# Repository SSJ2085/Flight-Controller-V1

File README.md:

# Flight-Controller-V1
This is a design of a flight controller for the  small 4'' to 5'' UAV.

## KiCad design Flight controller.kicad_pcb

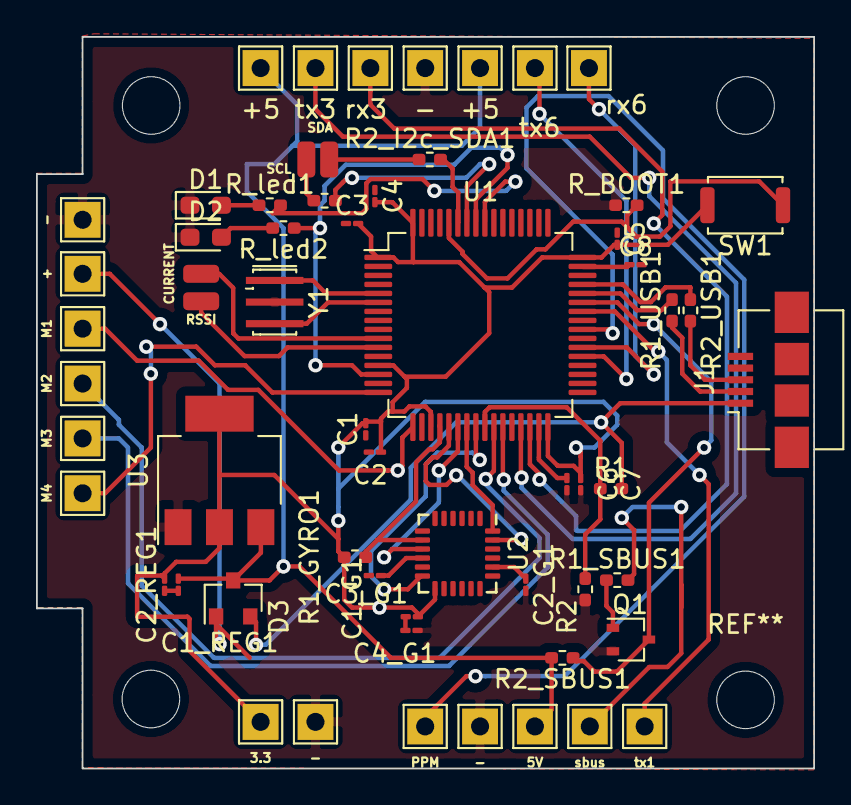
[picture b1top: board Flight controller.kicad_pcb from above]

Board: 2 copper layers, 43.2 x 40.6 mm, 60 parts (0 on the bottom side), 46 nets.

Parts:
3.3: 4; TestPoint_THTPad_2.0x2.0mm_Drill1.0mm
5V: TestPoint_THTPad_2.0x2.0mm_Drill1.0mm
+: +; TestPoint_THTPad_2.0x2.0mm_Drill1.0mm
+5, +5#2: TestPoint_THTPad_2.0x2.0mm_Drill1.0mm
-: 4; TestPoint_THTPad_2.0x2.0mm_Drill1.0mm
-#2: TestPoint_THTPad_2.0x2.0mm_Drill1.0mm
-#3: 4; TestPoint_THTPad_2.0x2.0mm_Drill1.0mm
-#4: -; TestPoint_THTPad_2.0x2.0mm_Drill1.0mm
C1, C2, C3, C4, C5, C6, C7, C8: 100nF; C_01005_0402Metric_Pad0.57x0.30mm_HandSolder
C1_G1, C3_G1: 0.1uF; C_01005_0402Metric_Pad0.57x0.30mm_HandSolder
C1_REG1, C2_REG1: 10uF; C_01005_0402Metric_Pad0.57x0.30mm_HandSolder
C2_G1: 2.2nF; C_01005_0402Metric_Pad0.57x0.30mm_HandSolder
C4_G1: 1uF; C_01005_0402Metric_Pad0.57x0.30mm_HandSolder
CURRENT: SolderWirePad_1x01_SMD_1x2mm
D1: LED_Small; LED_0603_1608Metric_Pad1.05x0.95mm_HandSolder
D2: LED; LED_0603_1608Metric_Pad1.05x0.95mm_HandSolder
D3: BAT54C; SOT-23
J1: USB_B_Micro; USB_Micro-B_Amphenol_10104110_Horizontal
M1: 1; TestPoint_THTPad_2.0x2.0mm_Drill1.0mm
M2: 2; TestPoint_THTPad_2.0x2.0mm_Drill1.0mm
M3: 3; TestPoint_THTPad_2.0x2.0mm_Drill1.0mm
M4: 4; TestPoint_THTPad_2.0x2.0mm_Drill1.0mm
PPM: 4; TestPoint_THTPad_2.0x2.0mm_Drill1.0mm
Q1: BC817W; SOT-323_SC-70
R1, R2: 10k; R_0402_1005Metric_Pad0.72x0.64mm_HandSolder
R1_GYRO1, R1_I2c_SCL1, R2_I2c_SDA1, R2_SBUS1: 10K; R_0402_1005Metric_Pad0.72x0.64mm_HandSolder
R1_SBUS1: 4.7K; R_0402_1005Metric_Pad0.72x0.64mm_HandSolder
R1_USB1, R2_USB1: 22; R_0402_1005Metric_Pad0.72x0.64mm_HandSolder
RSSI: SolderWirePad_1x01_SMD_1x2mm
R_BOOT1: 10k; R_0402_1005Metric_Pad0.72x0.64mm_HandSolder
R_led1, R_led2: 1K; R_0402_1005Metric_Pad0.72x0.64mm_HandSolder
SCL: SolderWirePad_1x01_SMD_1x2mm
SDA: SolderWirePad_1x01_SMD_1x2mm
SW1: SW_Push; SW_Push_SPST_NO_Alps_SKRK
U1: STM32F405RGT6; LQFP-64_10x10mm_P0.5mm
U2: MPU-6000; InvenSense_QFN-24_4x4mm_P0.5mm
U3: NCP1117-3.3_SOT223; SOT-223-3_TabPin2
Y1: 8MHZ; Resonator_SMD_muRata_CSTxExxV-3Pin_3.0x1.1mm_HandSoldering
rx3: TestPoint_THTPad_2.0x2.0mm_Drill1.0mm
rx6: 4; TestPoint_THTPad_2.0x2.0mm_Drill1.0mm
sbus: TestPoint_THTPad_2.0x2.0mm_Drill1.0mm
tx1, tx3, tx6: TestPoint_THTPad_2.0x2.0mm_Drill1.0mm

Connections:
+5V: +.2, D3.1, R2_SBUS1.2
/5V_USB: D3.2, J1.1, R1.2
/CURRENT_PAD: CURRENT.1, U1.10
/GYRO_CS: R1_GYRO1.1, U1.20, U2.8
/GYRO_INT: U1.24, U2.12
/GYRO_SCL: U1.21, U2.23
/GYRO_SDA: U1.23, U2.24
/GYRO_SDO: U1.22, U2.9
/I2C_SCL: R1_I2c_SCL1.1, SCL.1
/I2C_SDA: R2_I2c_SDA1.1, SDA.1
/LED1: R_led1.2, U1.56
/LED2: R_led2.1, U1.14, U1.57
/M1: M1.3, U1.17
/M2: M2.4, U1.26
/M3: M3.5, U1.27
/M4: M4.6, U1.16
/PPM_IN: PPM.PPM, U1.40
/RSSI: RSSI.1, U1.11
/SBUS: R1_SBUS1.2, sbus.1
/UART1_RX: Q1.3, R2_SBUS1.1, U1.43
/UART1_TX: U1.42, tx1.1
/UART3_RX: U1.30, rx3.RX3
/UART3_TX: U1.29, tx3.TX3
/UART6_RX: U1.38, rx6.RX6
/UART6_TX: U1.37, tx6.TX6
/VDD: 3.3.7, C1.2, C2.2, C2_REG1.2, C3.2, C3_G1.1, C4.2, C5.2, C6.2, R1_GYRO1.2, SW1.2, U1.1, U1.13, U1.19, U1.32, U1.48, U1.64, U2.13, U3.2
BOOT: R_BOOT1.2, SW1.1, U1.60
GND: -.6, -#2.GND, -#3.6, -#4.1, C1.1, C1_G1.2, C1_REG1.2, C2.1, C2_G1.2, C2_REG1.1, C3.1, C4.1, C4_G1.2, C5.1, C6.1, C7.1, C8.2, D1.1, D2.1, J1.5, Q1.2, R2.2, R_BOOT1.1, U1.12, U1.18, U1.63, U2.1, U2.11, U2.18, U3.1, Y1.2
unnamed: C1_G1.1, U2.10
unnamed: 5V.1, +5.+5, +5#2.+5, C1_REG1.1, D3.3, U3.3
unnamed: C2_G1.1, U2.20
unnamed: C3_G1.2, C4_G1.1
unnamed: C7.2, U1.31
unnamed: C8.1, U1.47
unnamed: D1.2, R_led1.1
unnamed: D2.2, R_led2.2
unnamed: J1.2, R1_USB1.1
unnamed: J1.3, R2_USB1.2
unnamed: Q1.1, R1_SBUS1.1
unnamed: R1.1, R2.1, U1.25
unnamed: R1_I2c_SCL1.2, U1.58
unnamed: R1_USB1.2, U1.44
unnamed: R2_I2c_SDA1.2, U1.59
unnamed: R2_USB1.1, U1.45
unnamed: U1.5, Y1.1
unnamed: U1.6, Y1.3
